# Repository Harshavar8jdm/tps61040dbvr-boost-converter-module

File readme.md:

# TPS61040 5V to 12V DC-DC Boost Converter

A compact (18 mm × 14 mm) 2-layer DC-DC step-up converter module designed around the Texas Instruments **TPS61040** boost switching regulator. Converts a nominal 5 V input rail to a regulated 12 V output for low-power electronics, sensor supplies, and display bias networks.

---

## Technical Specifications

| Parameter | Value | Notes |
| :--- | :--- | :--- |
| **Input Voltage ($V_{IN}$)** | 5.0 V nominal | Operating range: 1.8 V to 6.0 V |
| **Output Voltage ($V_{OUT}$)** | 12.06 V nominal | Configured via precision feedback divider |
| **Switch Current Limit** | 400 mA (peak) | Internal switch rating |
| **Control Scheme** | Constant Peak Current PFM | Switch frequency up to 1 MHz |
| **Quiescent Current** | 28 µA | Typical operating $I_Q$ |
| **Board Dimensions** | 18.0 mm × 14.0 mm | Dual-layer 1.6 mm FR4 |

---

## Visuals & Renders

### 3D Model Renders

| Top View | Bottom View |
| :---: | :---: |
|  |  |

---

## Schematic Design

### Circuit Details

1. **Feedback Network Calculation**:
   The output voltage is set using an internal reference voltage of $V_{FB} = 1.233\text{ V}$:
   $$V_{OUT} = V_{FB} \times \left(1 + \frac{R_1}{R_2}\right)$$
   
   Using $R_1 = 1.8\text{ M}\Omega$ and $R_2 = 205\text{ k}\Omega$:
   $$V_{OUT} = 1.233\text{ V} \times \left(1 + \frac{1,800,000}{205,000}\right) = 12.058\text{ V}$$

2. **Feedforward Compensation ($C_2$)**:
   A $4.7\text{ pF}$ ceramic capacitor ($C_2$) in parallel with $R_1$ compensates for parasitic capacitance at the high-impedance `FB` node, suppressing switching ripple and stabilizing the feedback loop.

3. **Power Stage Components**:
   - **Inductor ($L_1$)**: Murata LQH4C6R8M04 ($6.8\ \mu\text{H}$, $1812$ package). Chosen for low DC resistance and sufficient saturation current above the 400 mA switch limit.
   - **Rectifier Diode ($D_1$)**: ON Semiconductor MBR0530 Schottky diode ($30\text{ V}, 500\text{ mA}$, SOD-123). Low forward voltage drop ($V_F \approx 0.38\text{ V}$) maximizes power conversion efficiency.
   - **Filter Capacitors ($C_1, C_3$)**: $4.7\ \mu\text{F}$ 0805 MLCC capacitors for input decoupling and output ripple attenuation.

---

## PCB Layout & Design Considerations

* **Physical Dimensions**: 18.0 mm × 14.0 mm with standard 2.54 mm (100 mil) pin headers for input, output, and ground test points.
* **Switching Loop Minimization**: Pin 1 (`SW`), Inductor $L_1$, and Diode $D_1$ are placed tightly adjacent to reduce high $di/dt$ loop area and limit radiated Electromagnetic Interference (EMI).
* **Feedback Guarding**: Feedback resistor divider ($R_1, R_2$) and compensation capacitor ($C_2$) are located in close proximity to Pin 3 (`FB`). The feedback trace taps off downstream of output capacitor $C_3$ to avoid sensing high-frequency switching noise.

---

## Bill of Materials (BOM)

| RefDes | Qty | Value / Component | Package | Manufacturer | Part Number |
| :--- | :---: | :--- | :--- | :--- | :--- |
| **U1** | 1 | TPS61040 Boost Regulator IC | SOT-23-5 | Texas Instruments | `TPS61040DBVR` |
| **L1** | 1 | $6.8\ \mu\text{H}$ Power Inductor | 1812 / 4532 | Murata | `LQH4C6R8M04` |
| **D1** | 1 | $30\text{ V}, 500\text{ mA}$ Schottky Diode | SOD-123 | ON Semiconductor | `MBR0530` |
| **C1** | 1 | $4.7\ \mu\text{F}, 10\text{ V}$ X5R MLCC | 0805 | Taiyo Yuden | `JMK212BJ106MG` |
| **C3** | 1 | $4.7\ \mu\text{F}, 16\text{ V}$ X5R MLCC | 0805 | Taiyo Yuden | `EMK316BJ475ML` |
| **C2** | 1 | $4.7\text{ pF}, 50\text{ V}$ C0G MLCC | 0805 | Generic | — |
| **R1** | 1 | $1.8\text{ M}\Omega, 1\%$ Resistor | 0805 | Generic | — |
| **R2** | 1 | $205\text{ k}\Omega, 1\%$ Resistor | 0805 | Generic | — |
| **J1–J4** | 4 | 1-Pin Header (50 mil / 100 mil hole) | Through-hole | Generic | — |

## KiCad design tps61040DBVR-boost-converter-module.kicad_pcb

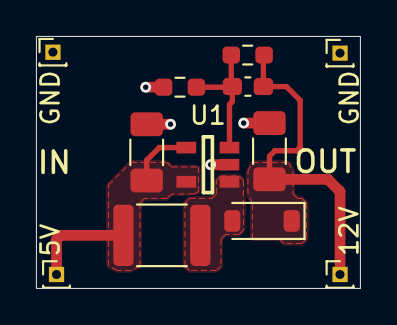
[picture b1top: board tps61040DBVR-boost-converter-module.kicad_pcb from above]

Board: 2 copper layers, 18.0 x 14.0 mm, 12 parts (0 on the bottom side), 5 nets.

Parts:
5V: +5V; PinHeader_1x01_P1.00mm_Vertical
12V: +12V; PinHeader_1x01_P1.00mm_Vertical
C1, C3: 4.7uF; C_1206_3216Metric_Pad1.33x1.80mm_HandSolder
C2: 4.7pF; C_0603_1608Metric_Pad1.08x0.95mm_HandSolder
D1: ON Semi MBR0530; D_SOD-123
GND: GND; PinHeader_1x01_P1.00mm_Vertical
GND#2: GND; PinHeader_1x01_P1.00mm_Vertical
L1: 6.8uH; L_1812_4532Metric
R1: 1.8M; R_0603_1608Metric_Pad0.98x0.95mm_HandSolder
R2: 205K; R_0603_1608Metric_Pad0.98x0.95mm_HandSolder
U1: TPS61040DBVR; DBV0005A

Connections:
+5V: 5V.1 (Pin_1_1), C1.1, L1.1, U1.4 (EN), U1.5 (VIN)
+12V: 12V.1 (Pin_1_1), C2.1, C3.1, D1.1 (K), R1.1
/FB: C2.2, R1.2, R2.1, U1.3 (FB)
/SW: D1.2 (A), L1.2, U1.1 (SW)
GND: C1.2, C3.2, GND.1 (Pin_1_1), GND#2.1 (Pin_1_1), R2.2, U1.2 (GND)
